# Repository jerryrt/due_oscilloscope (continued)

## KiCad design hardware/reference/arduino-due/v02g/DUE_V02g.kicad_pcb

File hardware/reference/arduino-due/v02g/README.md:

# Arduino Due V02g in KiCad

Open **[DUE_V02g.kicad_pcb](DUE_V02g.kicad_pcb)** directly in the
KiCad 10 PCB Editor to inspect the complete Due board, its headers,
components, copper and mounting holes. This is an alternate archived
revision. Use the [V03 PCB](../v03/Arduino-DUE-V03.kicad_pcb) as the working
reference for the owner's board; [selection evidence](../hardware-observations.json).

For the other retained board revision, open the separate
**[V03 KiCad PCB](../v03/Arduino-DUE-V03.kicad_pcb)**.
[V03 conversion notes and checks](../v03/README.md) document its source,
layer corrections and limitations. V03 now assigns 119 component bodies;
this alternate V02g reference has no 3D model assignments.

Arduino's [Due documentation](https://docs.arduino.cc/hardware/due/) links
to [this official CAD archive](https://docs.arduino.cc/static/f051671bbed80ddf7352991d62cb0d5c/A000056-cad-files.zip).
Downloaded on 2026-10-30, it contained **DUE_V02g** in EAGLE format.
The original extracted EAGLE files and license metadata are retained;
the ZIP itself was removed at the owner's request.
The KiCad board here is a local conversion using KiCad **10.0.6**;
it is not an Arduino-published native KiCad design.

| File | Purpose |
|---|---|
| `DUE_V02g.kicad_pcb` | Converted full Due PCB, with embedded footprints |
| `DUE_V02g.kicad_dru` | Importer-generated clearance rules; not a complete verified KiCad project setup |
| `source/DUE_V02g.brd` | Original EAGLE PCB |
| `source/DUE_V02g.sch` | Original EAGLE schematic; no native KiCad schematic conversion is included |
| `source/License.textClipping` | Publisher's original license metadata |
| `sources.json` | Source URL, date, sizes and SHA-256 hashes |
| `import-board.py` | Reproduce the conversion with KiCad 10.x |
| `check-board.py` | Verify source component positions, pad nets, native reload and SVG export |
| `import-report.json` | Original importer report, before the drawing-layer corrections below |
| `validation.json` | Component-position, pad-net and reload verification results |

Recreate the native board from the repository root:

```sh
python3 hardware/reference/arduino-due/v02g/import-board.py
```

Set `KICAD_CLI` if the required executable is not on PATH or at the default
macOS application location. Reimporting overwrites the converted PCB.

Verify using Python with KiCad 10's `pcbnew` module (bundled on this Mac):

```sh
/Applications/KiCad/KiCad.app/Contents/Frameworks/Python.framework/Versions/3.9/bin/python3 hardware/reference/arduino-due/v02g/check-board.py
```

## Conversion checks and limitations

All 141 source components are present at their original coordinates,
within 0.000002 mm serialization tolerance. All 605 source pad-to-net
assignments match. Six additional footprints represent the source's
six standalone holes. KiCad appends `0` to 15 references without a
numeric suffix, such as `POWER` becoming `POWER0`; the mapping is retained
in `validation.json`. Native-board reload and top-layer SVG export passed.

The importer reports no warnings or errors, but initially writes 140
plain-board graphics onto an `UNDEFINED` layer. The reproduction script
identifies their original layers by position and preserves them as:

- `User.1`: 139 graphics from EAGLE layer 114, `test-probe`.
- `User.2`: one line from EAGLE layer 42, `bRestrict`. This is a reference
  drawing only; it does **not** enforce a copper keepout in KiCad.

This is a reference conversion for inspecting the existing Due and
comparing shield geometry. The checks do not qualify the conversion for
fabrication or establish that a particular physical board revision matches.
Publisher copyright, trademark and license terms remain applicable.

The separate `Arduino-DUE-V03` source is extracted under
[`v03/source/`](../v03/source/), with its conversion under [`v03/`](../v03/README.md).
The revisions have different power-supply layouts and are not interchangeable.
The AFE shield PCB is in [`hardware/afe-proto`](../../../afe-proto/README.md). The
earlier [Mega proto carrier](../../../mega-proto-carrier/README.md) is kept for
reference only; the AFE no longer uses a proto board.

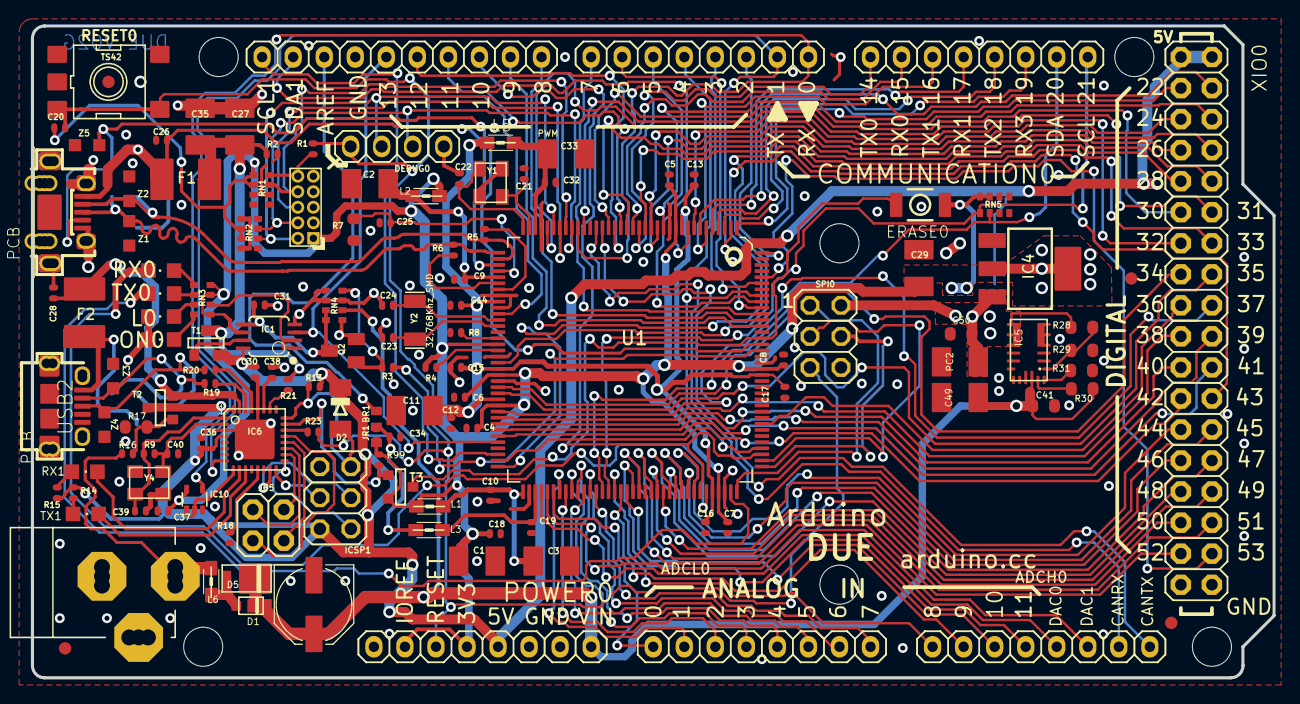
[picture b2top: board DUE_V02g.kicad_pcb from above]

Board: 2 copper layers, 101.6 x 53.3 mm, 147 parts (0 on the bottom side), 150 nets.

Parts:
ADCH0: FH254-108DF08500V; 1X08
ADCL0: FH254-108DF08500V; 1X08
BR1: NM; J0402
C1, C2, C3, C11, C27, C29, C33, C35, C49: 22uF; SMC_B
C4, C5, C6, C7, C8, C9, C10, C12, C13, C14, C15, C16, C17, C18, C19, C28, C30, C31, C32, C34, C36, C37: 100nF; C0402
C20, C26: 10n; C0402
C21, C22, C23, C24, C25, C39, C40: 22pF; C0402
C38: 1uF; C0402
C41, C50: 100nF; C0603-ROUND
CN2: PINHEAD-2x5-P1.27; PINHEAD_2X05_127
COMMUNICATION0: FH254-108DF08500V; 1X08
D1: MSS1P3L-M3/89A; MICROSMP
D2: CD1206-S01575; MINIMELF
D5: SS1P3L; DO220AAL
DEBUG0: PH1X4-THT
ERASE0: 157SW; SMD_157SW
F1, F2: MF-MSMF050-2 500mA; L1812
FID1, FID2, FID3, FID4: FIDUCIALMOUNT; FIDUCIA-MOUNT
IC1: LMV358IDGKR; MSOP08
IC4: NX1117CE33Z; SOT223
IC5: MPM3610; QFN-20
IC6: ATMEGA16U2-MU; MLF32
IC10: 74LVC1G125DCKR; SC70-5
ICSP1: ICSP; 2X03
JP5: 2x2M - NM; 2X02
JR1: 0R; R0402
L0: Yellow; CHIPLED_0805
L1, L2, L3, L5, L6: MH2029-300Y; 0805
ON0: Green; CHIPLED_0805
PC1: 47uF; PANASONIC_D
PC2: 22uF; SMC_B
POWER0: FH254-108DF08500V; 1X08
PWMH0: FH254-110DF08500V; 1X10
PWML0: FH254-108DF08500V; 1X08
Q2: BC847B; SOT23
R1, R8: 0R; R0402
R2, R13, R18, R99: 10K; R0402
R3, R14, R15, R21, R23: 1K; R0402
R4, R16: 100k; R0402
R5, R6: 39R 1%; R0402
R7: 6K8; R0603-ROUND
R9: 1M; R0402
R17: 75K; R0603-ROUND
R19, R20: 22R; R0402
R28: 100K_1%; R0603-ROUND
R29: 19K1_0,1%; R0603-ROUND
R30: 100k; R0603-ROUND
R31: 56k; R0603-ROUND
RESET0: TS42
RN1, RN2, RN4: 100k; CAY16
RN3: 1K; CAY16
RN5: 1K5; CAY16
RX0, RX1: Yellow; CHIPLED_0805
SPI0: ICSP; 2X03
T1, T2, T3: PMV48XP; SOT-23
TX0, TX1: Yellow; CHIPLED_0805
U1: ATSAM3X8EA-AU; LQFP144
U$1, U$2: DNP; FRAME
UD+1, UD+2: DNP; TP-1.00MM
UD-1, UD-2: DNP; TP-1.00MM
UGND1, UGND2: DNP; TP-1.00MM
UNK_HOLE_0: dummyfp0
UNK_HOLE_1: dummyfp1
UNK_HOLE_2: dummyfp2
UNK_HOLE_3: dummyfp3
UNK_HOLE_4: dummyfp4
UNK_HOLE_5: dummyfp5
USB1: MCR-AB1-S-RA-SMT-TR; MCR-AB1-S-RA-SMT
USB2: MCR-B-S-RA-SMT-CS1TR; CON2_USB_MICRO_B_AT
UVB1, UVB2: DNP; TP-1.00MM
X2: POWER-SUPPLY; POWERSUPPLY_DC-21MM
XIO0: 18x2F-H8.5; 2X18
Y1: 12mHz-12pF-K7; CRYSTAL-3.2-2.5
Y2: 32,768Khz_SMD; RESONATOR_EPSON_FC_145
Y4: 16Mhz-KX-7; CRYSTAL-3.2-2.5
Z1, Z2, Z3, Z4, Z5: BRNCG0603MLC-05E; CT_CN0603

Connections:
8PB4: IC6.18, JP5.1
8PB5: IC6.19, JP5.3
8PB6: IC6.20, JP5.2
8PB7: IC6.21, JP5.4
16U2-TX: IC6.9, IC10.1, IC10.2
+3V3: BR1.3, C1.+, C4.2, C5.2, C6.2, C7.2, C8.2, C18.2, C20.2, C29.+, C37.1, CN2.1, ERASE0.1, IC1.6, IC4.2, IC4.4, IC10.5, JR1.1, L1.1, L2.1, POWER0.2, POWER0.4, R4.2, R99.2, RN1.5, RN1.6, RN2.2, RN2.3, RN3.5, RN3.7, RN3.8, RN5.3, RN5.4, T3.2, U1.11, U1.52, U1.57, U1.62, U1.105, U1.125
+5V: C30.2, C36.1, C50.1, D2.C, IC1.8, IC4.3, IC5.7, IC5.8, IC5.9, IC5.20, IC6.4, IC6.32, ICSP1.2, PC2.+, POWER0.5, R13.2, R14.1, R15.1, R28.2, SPI0.2, T1.2, T2.1, XIO0.1, XIO0.2
AD0: ADCL0.1, U1.78
AD1: ADCL0.2, U1.79
AD2: ADCL0.3, U1.80
AD3: ADCL0.4, U1.81
AD4: ADCL0.5, U1.82
AD5: ADCL0.6, U1.83
AD6: ADCL0.7, U1.84
AD7: ADCL0.8, U1.85
AD8: ADCH0.1, U1.88
AD9: ADCH0.2, U1.89
AD10: ADCH0.3, U1.90
AD11(TXD3): ADCH0.4, U1.91
AD14(RXD3): U1.92, XIO0.33
AREF: BR1.1, PWMH0.8
AVREF: C19.2, L3.2, U1.75
AVREFL: BR1.2, C34.2, JR1.2, L3.1
BD+: R20.2, UD+2.X, USB2.P3, Z4.2
BD-: R19.2, UD-2.X, USB2.P2, Z3.2
CANRX0: ADCH0.7, U1.24
CANTX0: ADCH0.8, U1.23
CANTX1/IO: U1.140, XIO0.34
CMP: C31.2, IC1.5, Q2.3, RN4.3, RN4.4
D+: R6.1, U1.37, UD-1.X, USB1.3, Z1.1
D-: R5.1, U1.38, UD+1.X, USB1.2, Z2.1
DAC0(CANRX1): ADCH0.5, U1.76
DAC1: ADCH0.6, U1.77
DTR: IC6.13, R18.1
ERASE_CMD: IC6.23, R99.1, T3.3
ERASE_S: ERASE0.2, T3.1, U1.130
GATE_CMD: IC1.7, T1.3
GND: C1.-, C2.-, C3.-, C4.1, C5.1, C6.1, C7.1, C8.1, C9.1, C10.1, C11.-, C12.1, C13.1, C14.1, C15.1, C16.1, C17.1, C18.1, C19.1, C21.2, C22.2, C23.2, C24.2, C25.2, C26.2, C27.-, C28.2, C29.-, C30.1, C31.1, C32.1, C33.-, C34.1, C35.-, C36.2, C37.2, C38.2, C39.2, C40.2, C41.2, C49.-, C50.2, CN2.3, CN2.5, CN2.9, DEBUG0.1, IC1.4, IC4.1, IC5.3, IC5.12, IC5.13, IC5.14, IC6.3, IC6.28, IC6.33, IC10.3, ICSP1.6, L0.C, ON0.C, PC1.-, PC2.-, POWER0.6, POWER0.7, PWMH0.7, Q2.2, R2.1, R7.1, R8.1, R17.1, R18.2, R29.1, R31.1, RESET0.1, RESET0.2, RN1.1, RN1.2, RN1.7, RN1.8, RN2.1, RN2.4, RN2.5, RN2.8, RN4.1, RN4.2, RN4.5, RN4.7, SPI0.6, U1.12, U1.33, U1.44, U1.46, U1.54, U1.58, U1.74, U1.106, U1.126, UGND1.X, UGND2.X, USB1.5, USB1.P$1, USB1.P$2, USB1.P$3, USB1.P$4, USB1.P$5, USB1.P$6, USB1.P$7, USB1.P$8, USB1.P$9, USB1.P$10, USB1.P$11, USB1.S1, USB1.S2, USB1.S3, USB1.S4, USB2.P5, USB2.P$1, USB2.P$2, USB2.P$3, USB2.P$4, USB2.P$5, USB2.P$6, USB2.P$7, USB2.P$8, USB2.S1, USB2.S2, USB2.S3, USB2.S4, USB2.S5, USB2.S6, X2.1, X2.3, XIO0.35, XIO0.36, Y1.2, Y1.4, Y4.2, Y4.4, Z1.2, Z2.2, Z3.1, Z4.1, Z5.1
JTAG_RESET: CN2.10, R1.1, RN1.4
JTAG_TCK: CN2.4, DEBUG0.2, RN2.7, U1.28
JTAG_TDI: CN2.8, RN1.3, U1.29
JTAG_TDO: CN2.6, U1.30
JTAG_TMS: CN2.2, DEBUG0.3, RN2.6, U1.31
L13: IC1.1, IC1.2, RN3.6
MASTER-RESET: C20.1, DEBUG0.4, POWER0.3, R1.2, R23.2, RESET0.3, RESET0.4, SPI0.5, U1.47
MISO: SPI0.1, U1.108
MISO2: IC6.17, ICSP1.1
MOSI: SPI0.4, U1.109
MOSI2: IC6.16, ICSP1.4
unnamed: IC6.26, R21.1
unnamed: L0.A, RN3.3
unnamed: ON0.A, RN3.4
unnamed: R15.2, RX1.A
unnamed: R8.2, U1.51
unnamed: Q2.1, R3.2, RN4.8
unnamed: R4.1, U1.53
unnamed: D1.A, D5.P$2, L6.1
unnamed: R5.2, U1.43
unnamed: R6.2, U1.42
unnamed: R14.2, TX1.A
unnamed: R16.1, R17.2, T2.3
unnamed: IC5.1, R28.1, R29.2
unnamed: IC5.17, R30.2
unnamed: IC5.18, R31.2
unnamed: RN3.1, RX0.A
unnamed: RN3.2, TX0.A
PIN22: U1.1, XIO0.3
PIN23: U1.7, XIO0.4
PIN24: U1.8, XIO0.5
PIN25: U1.13, XIO0.6
PIN26: U1.14, XIO0.7
PIN27: U1.15, XIO0.8
PIN28: U1.16, XIO0.9
PIN29: U1.19, XIO0.10
PIN30: U1.22, XIO0.11
PIN31: U1.26, XIO0.12
PIN32: U1.32, XIO0.13
PIN33: U1.55, XIO0.14
PIN34: U1.59, XIO0.15
PIN35: U1.60, XIO0.16
PIN36: U1.116, XIO0.17
PIN37: U1.63, XIO0.18
PIN38: U1.64, XIO0.19
PIN39: U1.65, XIO0.20
PIN40: U1.66, XIO0.21
PIN41: U1.67, XIO0.22
PIN42: U1.71, XIO0.23
PIN43: U1.72, XIO0.24
PIN44: U1.101, XIO0.25
PIN45: U1.100, XIO0.26
PIN46: U1.99, XIO0.27
PIN47: U1.98, XIO0.28
PIN48: U1.97, XIO0.29
PIN49: U1.96, XIO0.30
PIN50: U1.95, XIO0.31
PIN51: U1.94, XIO0.32
PWM2: PWML0.3, U1.144
PWM3: PWML0.4, U1.139
PWM5: PWML0.6, U1.136
PWM6: PWML0.7, U1.135
PWM7: PWML0.8, U1.134
PWM8: PWMH0.1, U1.133
PWM9: PWMH0.2, U1.132
PWM11: PWMH0.4, U1.20
PWM12: PWMH0.5, U1.21
PWM13: IC1.3, PWMH0.6, U1.68
RD+: IC6.29, R20.1
RD-: IC6.30, R19.1
RESET2: D2.A, IC6.24, ICSP1.5, R13.1
RESET_CMD: IC6.22, R23.1
RX: IC10.4, PWML0.1, U1.27
RXD0: COMMUNICATION0.2, U1.18
RXD1: COMMUNICATION0.4, U1.5
RXD2: COMMUNICATION0.6, U1.3
RXL: RX0.C, U1.103
RXL-U2: IC6.10, RX1.C
SCK2: IC6.15, ICSP1.3
SCL0-3: COMMUNICATION0.8, RN5.5, U1.87
SCL1: PWMH0.10, U1.70
SDA0-3: COMMUNICATION0.7, RN5.6, U1.86
SDA1: PWMH0.9, U1.9
SPCK: SPI0.3, U1.110
SS0/PWM10: PWMH0.3, U1.102, U1.111
SS1/PWM4: PWML0.5, U1.112, U1.137
TX: IC6.8, PWML0.2, U1.2
TXD0: COMMUNICATION0.1, U1.17
TXD1: COMMUNICATION0.3, U1.6
TXD2: COMMUNICATION0.5, U1.4
TXL: TX0.C, U1.107
TXL-U2: IC6.11, TX1.C
UOTGID: U1.129, USB1.4, Z5.2
UOTGVBOF: R3.1, U1.128
USBVCC: C27.+, C35.+, F1.1, R2.2, R21.2, T1.1
USBVCCU2: C28.1, F2.1, IC6.31, T2.2
VBG: C25.1, R7.2, U1.40
VDDANA: C3.+, C10.2, L1.2, U1.73
VDDOUT: C11.+, C12.2, C13.2, C14.2, C15.2, C16.2, C17.2, L5.1, U1.10, U1.45, U1.56, U1.61, U1.104, U1.124
VDDOUTMI: C2.+, C9.2, L2.2, U1.41
VDDPLL: C32.2, C33.+, L5.2, U1.34
VIN: C41.1, C49.+, D1.K, D5.P$1, IC5.16, PC1.+, POWER0.8, R30.1, RN4.6
VIN+: L6.2, R16.2, X2.2
VUCAP: C38.1, IC6.27
XIN: C22.1, U1.36, Y1.1
XIN32: C24.1, U1.48, Y2.P$2
XOUT: C21.1, U1.35, Y1.3
XOUT32: C23.1, U1.49, Y2.P$1
XT1: C39.1, IC6.1, R9.1, Y4.1
XT2: C40.1, IC6.2, R9.2, Y4.3
XUSB: C26.1, F1.2, U1.39, USB1.1, UVB1.X
XVCC: F2.2, USB2.P1, UVB2.X
